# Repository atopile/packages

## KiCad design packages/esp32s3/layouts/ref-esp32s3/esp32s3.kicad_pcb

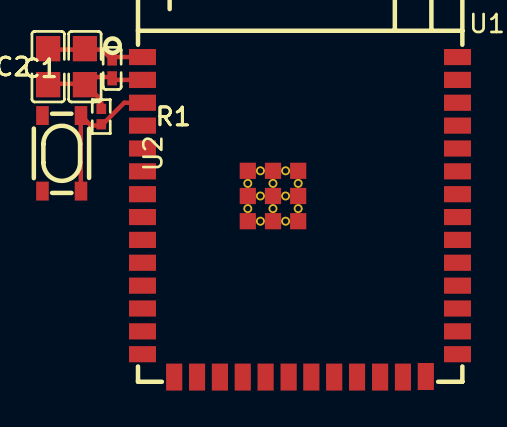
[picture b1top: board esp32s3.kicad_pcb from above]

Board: 2 copper layers, 6 parts (0 on the bottom side), 3 nets.

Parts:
C1: 100nF ±10% 16V X7R; C0402-b3ef17
C2, C3: 10µF ±10% 25V X5R; C0805-3b2e55
R1: 10kΩ ±1% 62.5mW; R0402-56259e
U1: WIRELM-SMD_ESP32-S3-WROOM-1
U2: KEY-SMD_4P-L4.2-W3.2-P2.20-LS4.6

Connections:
gnd: C1.2, C2.2, C3.2, U1.1, U1.40, U1.41, U2.3, U2.4
hv: C1.1, C2.1, C3.1, R1.1, U1.2
in: R1.2, U2.1, U2.2

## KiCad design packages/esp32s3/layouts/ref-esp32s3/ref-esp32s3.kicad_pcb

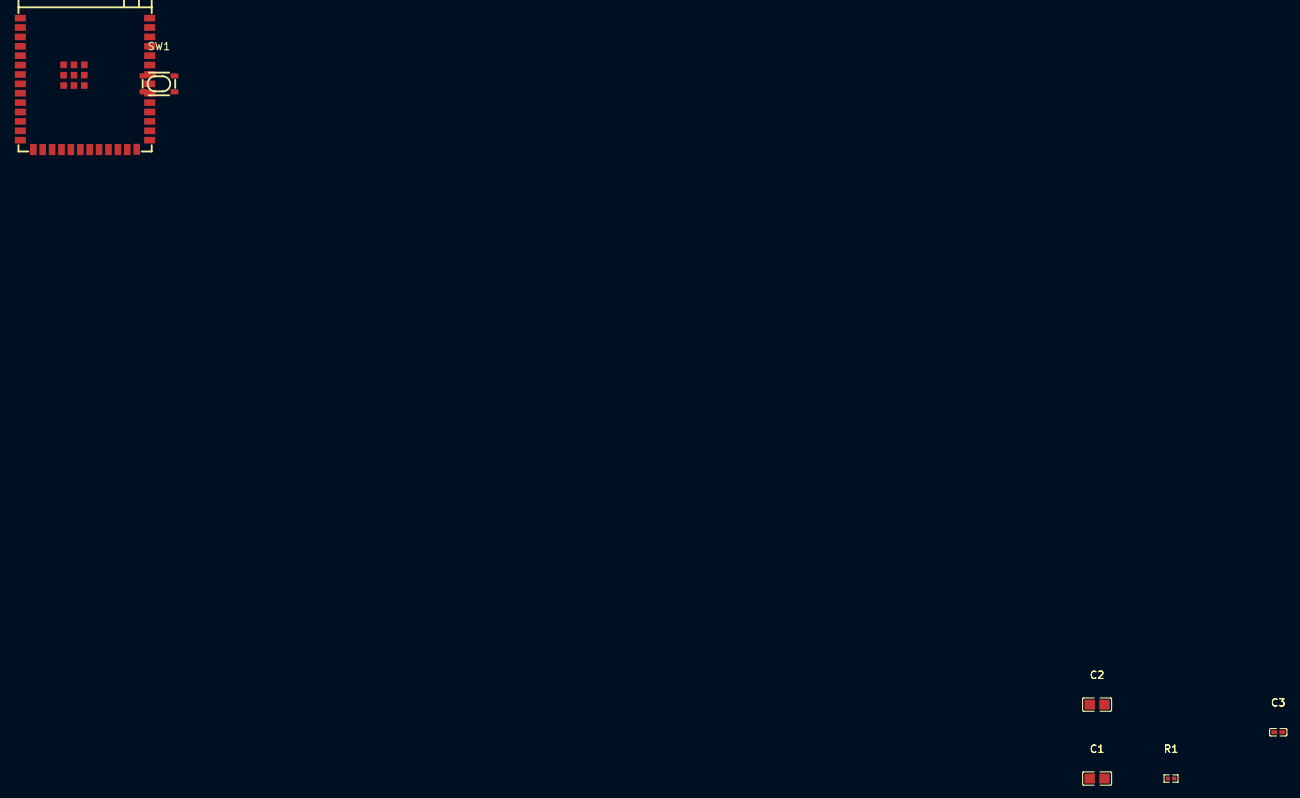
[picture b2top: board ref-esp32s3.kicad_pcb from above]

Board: 2 copper layers, 6 parts (0 on the bottom side), 4 nets, no tracks yet.

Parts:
C1, C2: 10µF ±10% 25V X5R; C0805
C3: 100nF ±10% 16V X7R; C0402
R1: 10kΩ ±1% 62.5mW; R0402
SW1: KEY-SMD_4P-L4.2-W3.2-P2.20-LS4.6
U1: WIRELM-SMD_ESP32-S3-WROOM-1

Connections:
EN: SW1.1, SW1.2, U1.3
gnd: C1.2, C2.2, C3.2, U1.1, U1.40, U1.41
hv: C1.1, C2.1, C3.1, R1.2, U1.2
net: R1.1, SW1.3, SW1.4

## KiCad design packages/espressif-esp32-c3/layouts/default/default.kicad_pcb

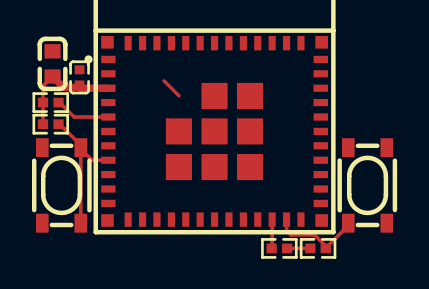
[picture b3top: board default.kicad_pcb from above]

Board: 2 copper layers, 9 parts (0 on the bottom side), 6 nets.

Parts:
C3: 2.2e-±20.0%F; C0603
C4: 1±10.0%F; C0402
R1, R2, R3: 10000±1.0%Ω; R0402
R4: 5100±1.0%Ω; R0402
SW1, SW2: KEY-SMD_4P-L4.2-W3.2-P2.20-LS4.6
U1: WIFIM-SMD_ESP32-C3-MINI-1

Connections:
DATA_1: R1.1, U1.5
MISO: R2.1, U1.22
N_TRST: R3.2, SW2.3, SW2.4, U1.8
hv: C3.1, C4.1, R1.2, R2.2, R3.1, R4.1, U1.3
lv: C3.2, C4.2, SW1.1, SW1.2, SW2.1, SW2.2, U1.1, U1.2, U1.11, U1.14, U1.36, U1.37, U1.38, U1.39, U1.40, U1.41, U1.42, U1.43, U1.44, U1.45, U1.46, U1.47, U1.48, U1.49, U1.50, U1.51, U1.52, U1.53
output: R4.2, SW1.3, SW1.4, U1.23

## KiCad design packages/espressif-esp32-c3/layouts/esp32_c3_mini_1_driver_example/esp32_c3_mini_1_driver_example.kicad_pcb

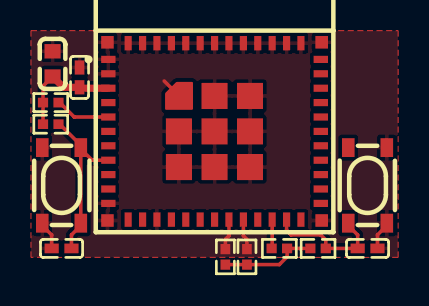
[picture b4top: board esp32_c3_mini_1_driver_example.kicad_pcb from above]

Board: 2 copper layers, 13 parts (0 on the bottom side), 8 nets.

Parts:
C1, C4: 100nF ±10% 16V X7R; C0402
C2: 1µF ±10% 25V X5R; C0402
C3: 22µF ±20% 6.3V X5R; C0603
R1, R2, R3, R4, R5: 10kΩ ±1% 62.5mW; R0402
R6: 5.1kΩ ±1% 62.5mW; R0402
SW1, SW2: KEY-SMD_4P-L4.2-W3.2-P2.20-LS4.6
U1: WIFIM-SMD_ESP32-C3-MINI-1

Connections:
GND: C1.1, C2.1, C3.2, C4.2, SW1.1, SW1.2, SW2.1, SW2.2, U1.1, U1.2, U1.11, U1.14, U1.36, U1.37, U1.38, U1.39, U1.40, U1.41, U1.42, U1.43, U1.44, U1.45, U1.46, U1.47, U1.48, U1.49, U1.50, U1.51, U1.52, U1.53
MISO: R2.1, U1.22
N_TRST: C2.2, R3.2, SW2.3, SW2.4, U1.8
SCL: R5.2, U1.20
SDA: R4.2, U1.19
VCC: C3.1, C4.1, R1.2, R2.2, R3.1, R4.1, R5.1, R6.1, U1.3
data_1: R1.1, U1.5
output: C1.2, R6.2, SW1.3, SW1.4, U1.23

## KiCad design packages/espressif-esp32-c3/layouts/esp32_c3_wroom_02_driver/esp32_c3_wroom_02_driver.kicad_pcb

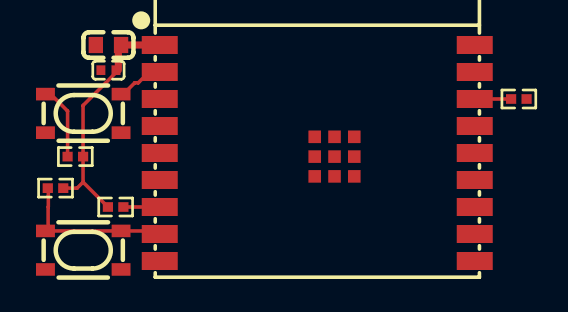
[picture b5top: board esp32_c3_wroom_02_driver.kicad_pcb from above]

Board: 2 copper layers, 9 parts (0 on the bottom side), 6 nets.

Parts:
C3: 22µF ±20%; C0603
C4: 100nF ±10%; C0402
R1, R2, R3: 10kΩ ±1%; R0402
R4: 5.1kΩ ±1%; R0402
SW1, SW2: KEY-SMD_4P-L4.2-W3.2-P2.20-LS4.6
U1: WIFIM-SMD_18P-L20.0-W18.0-P1.50

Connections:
DATA_1: R1.1, U1.16
MISO: R2.1, U1.7
N_TRST: R3.2, SW2.3, SW2.4, U1.2
hv: C3.1, C4.1, R1.2, R2.2, R3.1, R4.1, U1.1
lv: C3.2, C4.2, SW1.1, SW1.2, SW2.1, SW2.2, U1.9, U1.19
output: R4.2, SW1.3, SW1.4, U1.8

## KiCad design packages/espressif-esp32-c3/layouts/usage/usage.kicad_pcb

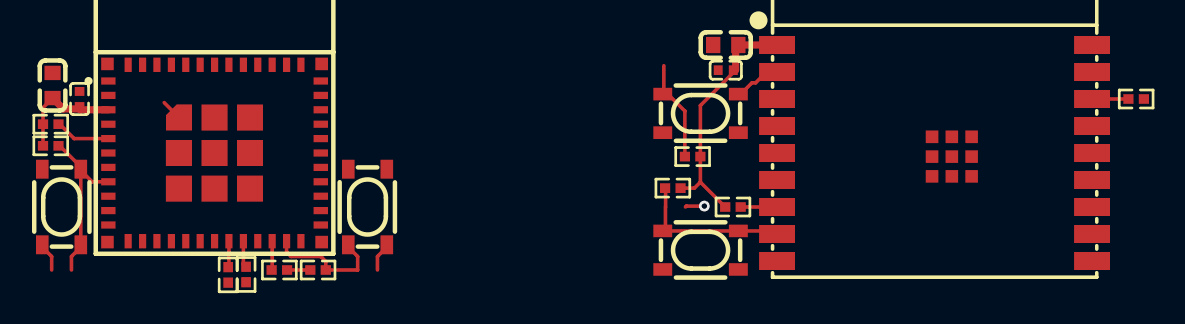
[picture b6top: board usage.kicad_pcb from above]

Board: 2 copper layers, 20 parts (0 on the bottom side), 17 nets.

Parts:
C2, C6: 22µF ±20%; C0603
C3, C7: 100nF ±10%; C0402
R1, R2, R4, R5, R6, R7, R8, R10: 10kΩ ±1%; R0402
R3, R9: 5.1kΩ ±1%; R0402
SW1, SW2, SW3, SW4: KEY-SMD_4P-L4.2-W3.2-P2.20-LS4.6
U1: WIFIM-SMD_ESP32-C3-MINI-1
U2: WIFIM-SMD_18P-L20.0-W18.0-P1.50

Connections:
DATA_1: R1.1, U1.5
MISO: R2.1, R8.1, U1.22, U2.7
MOSI: U1.21, U2.6
N_TRST: R4.2, SW2.3, SW2.4, U1.8
SCK: U1.12, U2.18
SCL: R6.2, U1.20, U2.5
SCLK: U1.16, U2.10
SD: U1.13, U2.17
SDA: R5.2, U1.19, U2.4
WS: U1.6, U2.15
hv: R5.1, R6.1
lv: C2.2, C3.2, C6.2, C7.2, SW1.1, SW1.2, SW2.1, SW2.2, SW3.1, SW3.2, SW4.1, SW4.2, U1.1, U1.2, U1.11, U1.14, U1.36, U1.37, U1.38, U1.39, U1.40, U1.41, U1.42, U1.43, U1.44, U1.45, U1.46, U1.47, U1.48, U1.49, U1.50, U1.51, U1.52, U1.53, U2.9, U2.19
output: R3.2, SW1.3, SW1.4, U1.23
power-hv: C2.1, C3.1, C6.1, C7.1, R1.2, R2.2, R3.1, R4.1, R7.2, R8.2, R9.1, R10.1, U1.3, U2.1
wroom_module-gpio[9]-output: R9.2, SW3.3, SW3.4, U2.8
wroom_module-jtag-N_TRST: R10.2, SW4.3, SW4.4, U2.2
wroom_module-mspi[2]-DATA_1: R7.1, U2.16
